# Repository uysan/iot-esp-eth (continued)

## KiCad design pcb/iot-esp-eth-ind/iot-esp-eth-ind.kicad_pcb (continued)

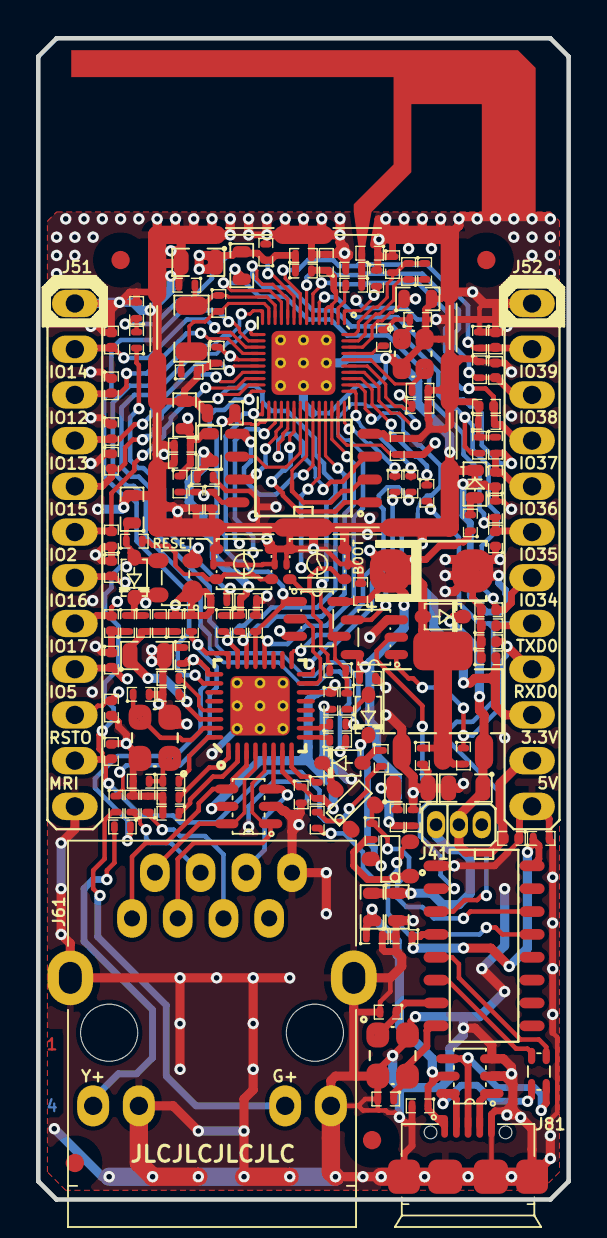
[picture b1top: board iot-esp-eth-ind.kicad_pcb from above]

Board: 4 copper layers, 29.5 x 64.5 mm, 150 parts (0 on the bottom side), 97 nets.

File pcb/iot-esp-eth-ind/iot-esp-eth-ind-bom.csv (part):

"Reference","Quantity","Value","Footprint","Datasheet","Digikey","Manufacturer","PartNumber","Power","Temperature","Tolerance"
"C1",1,"0.9pF/50V","Celebi:SM0402C","https://www.we-online.com/catalog/datasheet/885392005022.pdf","!13-CC0402BRNPO9BNR90CT-ND","Wurth",885392005022,"_","-55+125°C","0.1pF"
"C12,C13",2,"12pF/50V","Celebi:SM0402C","https://www.yageo.com/en/Chart/Download/pdf/CC0402JRNPO9BN120","311-1016-1-ND","Yageo","CC0402JRNPO9BN120","_","-55+125°C","5%"
"C14,C15,C69,C70",4,"18pF/50V","Celebi:SM0402C","https://www.yageo.com/en/Chart/Download/pdf/CC0402JRNPO9BN180","311-1415-1-ND","Yageo","CC0402JRNPO9BN180","_","-55+125°C","5%"
"C10,C16,C17,C2,C20,C25,C3,C31,C43,C5,C62,C63,C64,C65,C66,C67,C68,C71,C74,C75,C86,C87,C88,C90",24,"100nF/16V","Celebi:SM0402C","http://weblib.samsungsem.com/mlcc/mlcc-ec-data-sheet.do?part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","1276-1001-1-ND","Samsung","CL05B104KO5NNNC","_","-55+125°C","10%"
"C21,C41,C72,C89",4,"10uF/16V","Celebi:SM0805C","http://weblib.samsungsem.com/mlcc/mlcc-ec-data-sheet.do?part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","1276-2872-1-ND","Samsung","CL21B106KOQNNNE","_","-55+125°C","10%"
"C32",1,"100nF/50V","Celebi:SM0603C","http://weblib.samsungsem.com/mlcc/mlcc-ec-data-sheet.do?part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","1276-1000-1-ND","Samsung","CL10B104KB8NNNC","_","-55+125°C","10%"
"C4,C7",2,"3.3nF/50V","Celebi:SM0402C","http://weblib.samsungsem.com/mlcc/mlcc-ec-data-sheet.do?part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","1276-1552-1-ND","Samsung","CL05B332KB5NNNC","_","-55+125°C","10%"
"C42",1,"47uF/16V","Celebi:SMD-C-6032","https://spicat.kyocera-avx.com/product/tan/chartview/TAJC476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","478-1718-1-ND","Kyocera_AVX","TAJC476K016RNJ","_","-55+125°C","10%"
"C6",1,"10nF/50V","Celebi:SM0402C","https://www.yageo.com/en/Chart/Download/pdf/CC0402KRX7R9BB103","311-1349-1-ND","Yageo","CC0402KRX7R9BB103","_","-55+125°C","10%"
"C11,C18,C22,C8,C83",5,"1uF/16V","Celebi:SM0603C","https://www.yageo.com/en/Chart/Download/pdf/CC0603KRX7R7BB105","311-1446-1-ND","Yageo","CC0603KRX7R7BB105","_","-55+125°C","10%"
"C81",1,"100nF/50V","Celebi:SM0402C","https://www.yageo.com/en/Chart/Download/pdf/CC0402KRX7R9BB104","311-3566-1-ND","Yageo","CC0402KRX7R9BB104","_","-55+125°C","10%"
"C84,C85",2,"27pF/50V","Celebi:SM0402C","https://www.yageo.com/en/Chart/Download/pdf/CC0402JRNPO9BN270","311-1019-1-ND","Yageo","CC0402JRNPO9BN270","_","-55+125°C","5%"
"C19,C23,C24,C73,C82,C9",6,"15pF/50V","Celebi:SM0402C","https://www.yageo.com/en/Chart/Download/pdf/CC0402JRNPO9BN150","311-1017-1-ND","Yageo","CC0402JRNPO9BN150","_","-55+125°C","5%"
"D1",1,"TVS_4V","Celebi:SM0402V","https://www.murata.com/products/productdata/8796832759838/CR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","490-13210-2-ND","Murata","LXES15AAA1-153","15kV","-40+85°C","_"
"D31,D41,D82,D83",4,"BAT54WS","Celebi:SOD323","https://www.panjit.com.tw/upload/datasheet/BAT54WS.pdf","3757-BAT54WS_R1_00001CT-ND","Panjit","BAT54WS_R1_00001","0.2A","-55+125°C","_"
"D42",1,"Diode-LED_Green","Celebi:led-SM0603_Green","https://optoelectronics.liteon.com/upload/download/DS22-2000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","160-1446-1-ND","Liteon","LTST-C191KGKT","0.075W","-55+85°C","_"
"D61,D81",2,"TVS_5V","Celebi:SOT23-6L","https://www.we-online.com/catalog/datasheet/824015.pdf","732-4467-1-ND","Wurth",824015,"12A","-55+125°C","_"
"D100,D101,D102,D103,D104,D105,D106,D107,D108,D109,D110,D91,D92,D93,D94,D95,D96,D97,D98,D99",20,"TVS_5V","Celebi:DFN1006-2","https://en.leiditech.com/u_file/file/products/2212/16/1ac2f9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","!490-12804-1-ND","Leiditech","ULC0511CDN","110W","-55+150°C","_"
"E41",1,"Jumper","Celebi:N.A.","https://datasheet.lcsc.com/lcsc/2201121830_XKB-Connectivity-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","!S9345-ND","XKB","X1301-B1NIB","1A","-40+105°C","_"
"J41",1,"Conn_01x03","Celebi:sil-1.27mm-3P","https://www.helloxkb.com/public/images/pdf/X1311WV-XXJ-C18D27.pdf","!SAM10238-ND","XKB","X1311WV-03J-C18D27","1A","-40+105°C","_"
"J51,J52",2,"Conn_01x12/DNP","Celebi:sil-12P","https://www.helloxkb.com/public/images/pdf/X6511WV-XXH-C60D30.pdf","!S1012EC-12-ND","XKB","X6511WV-12H-C60D30","3A","-40+105°C","_"
"J61",1,74980111212,"Celebi:eth-74980111212","https://www.we-online.com/catalog/datasheet/74980111212.pdf","_","Wurth",74980111212,"_","-40+85°C","_"
"J81",1,"USB-Micro","Celebi:usb-629105136821","https://www.we-online.com/catalog/datasheet/629105136821.pdf","732-3155-1-ND","Wurth",629105136821,"1A","-40+105°C","_"
"L1",1,"2.2nH","Celebi:SM0402L","https://www.we-online.com/catalog/datasheet/7447840022G.pdf","732-7447840022GCT-ND","Wurth","7447840022G","0.3A","-55+125°C","0.1nH"
"L2,L81",2,"Bead_300R","Celebi:SM0603L","https://www.we-online.com/catalog/datasheet/742792641.pdf","732-1592-1-ND","Wurth",742792641,"2A","-55+125°C","25%"
"L3",1,"2nH","Celebi:SM0402L","https://www.we-online.com/catalog/datasheet/744765020A.pdf","732-1705-1-ND","Wurth","744765020A","1.04A","-40+125°C","0.2nH"
"L4",1,"Bead_220R/DNP","Celebi:SM0402L","https://www.we-online.com/catalog/datasheet/742792780.pdf","732-1569-1-ND","Wurth",742792780,"0.3A","-55+125°C","25%"
"L61,L82",2,"Bead_220R","Celebi:SM0402L","https://www.we-online.com/catalog/datasheet/742792780.pdf","732-1569-1-ND","Wurth",742792780,"0.3A","-55+125°C","25%"
"M1",1,"Shield_Cover","Celebi:N.A.","https://www.we-online.com/catalog/datasheet/36003160s.pdf","732-11644-1-ND","Wurth","36003160S","_","-40+125°C","_"
"Q81,Q82",2,"BC817","Celebi:SOT23-3","https://assets.nexperia.com/documents/data-sheet/BC817_SER.pdf","1727-2919-1-ND","Nexperia","BC817-40-215","0.5A","-65+150°C","_"
"R1",1,"20k","Celebi:SM0402","https://www.yageo.com/upload/media/product/productsearch/dat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","311-20.0KLRCT-ND","Yageo","RC0402FR-0720KL","1/16W","-55+155°C","1%"
"R2",1,"499R","Celebi:SM0402","https://www.yageo.com/upload/media/product/productsearch/dat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","311-499LRCT-ND","Yageo","RC0402FR-07499RL","1/16W","-55+155°C","1%"
"R3,R32",2,"100R","Celebi:SM0402","https://www.yageo.com/upload/media/product/productsearch/dat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","311-100LRCT-ND","Yageo","RC0402FR-07100RL","1/16W","-55+155°C","1%"
"R31",1,"100k","Celebi:SM0402","https://www.yageo.com/upload/media/product/productsearch/dat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","311-100KLRCT-ND","Yageo","RC0402FR-07100KL","1/16W","-55+155°C","1%"
"R4",1,"0R","Celebi:SM0402","https://www.yageo.com/upload/media/product/productsearch/dat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","311-0.0JRCT-ND","Yageo","RC0402JR-070RL","1/16W","-55+155°C","Jumper"
"R41",1,"2k7","Celebi:SM0402","https://www.yageo.com/upload/media/product/productsearch/dat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","311-2.70KLRCT-ND","Yageo","RC0402FR-072K7L","1/16W","-55+155°C","1%"
"R5",1,"10Meg","Celebi:SM0402","https://www.yageo.com/upload/media/product/productsearch/dat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","311-10.0MLRCT-ND","Yageo","RC0402FR-0710ML","1/16W","-55+155°C","1%"
"R51,R52,R53,R54,R55,R56",6,"470k","Celebi:SM0402","https://www.yageo.com/upload/media/product/productsearch/dat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","311-470KLRCT-ND","Yageo","RC0402FR-07470KL","1/16W","-55+155°C","1%"
"R6,R62,R63,R83,R84",5,"1k","Celebi:SM0402","https://www.yageo.com/upload/media/product/productsearch/dat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","311-1.00KLRCT-ND","Yageo","RC0402FR-071KL","1/16W","-55+155°C","1%"
"R64",1,"2k49","Celebi:SM0402","https://www.yageo.com/upload/media/product/productsearch/dat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","311-2.49KLRCT-ND","Yageo","RC0402FR-072K49L","1/16W","-55+155°C","1%"
"R65,R85",2,"47k","Celebi:SM0402","https://www.yageo.com/upload/media/product/productsearch/dat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","311-47.0KLRCT-ND","Yageo","RC0402FR-0747KL","1/16W","-55+155°C","1%"
"R66,R67,R81,R82",4,"10k","Celebi:SM0402","https://www.yageo.com/upload/media/product/productsearch/dat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","311-10.0KLRCT-ND","Yageo","RC0402FR-0710KL","1/16W","-55+155°C","1%"
"R68,R69,R7,R70,R8",5,"22R","Celebi:SM0402","https://www.yageo.com/upload/media/product/productsearch/dat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","311-22.0LRCT-ND","Yageo","RC0402FR-0722RL","1/16W","-55+155°C","1%"
"R71,R72,R73",3,"4k7","Celebi:SM0402","https://www.yageo.com/upload/media/product/productsearch/dat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","311-4.7KLRCT-ND","Yageo","RC0402FR-074K7L","1/16W","-55+155°C","1%"
"S1,S31",2,"Tact_Switch","Celebi:switch-WE-WS-TASV-3x2.6_H1.4mm","https://www.we-online.com/catalog/datasheet/435171014816.pdf","732-435171014816CT-ND","Wurth",435171014816,"0.05A","-40+85°C","_"
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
